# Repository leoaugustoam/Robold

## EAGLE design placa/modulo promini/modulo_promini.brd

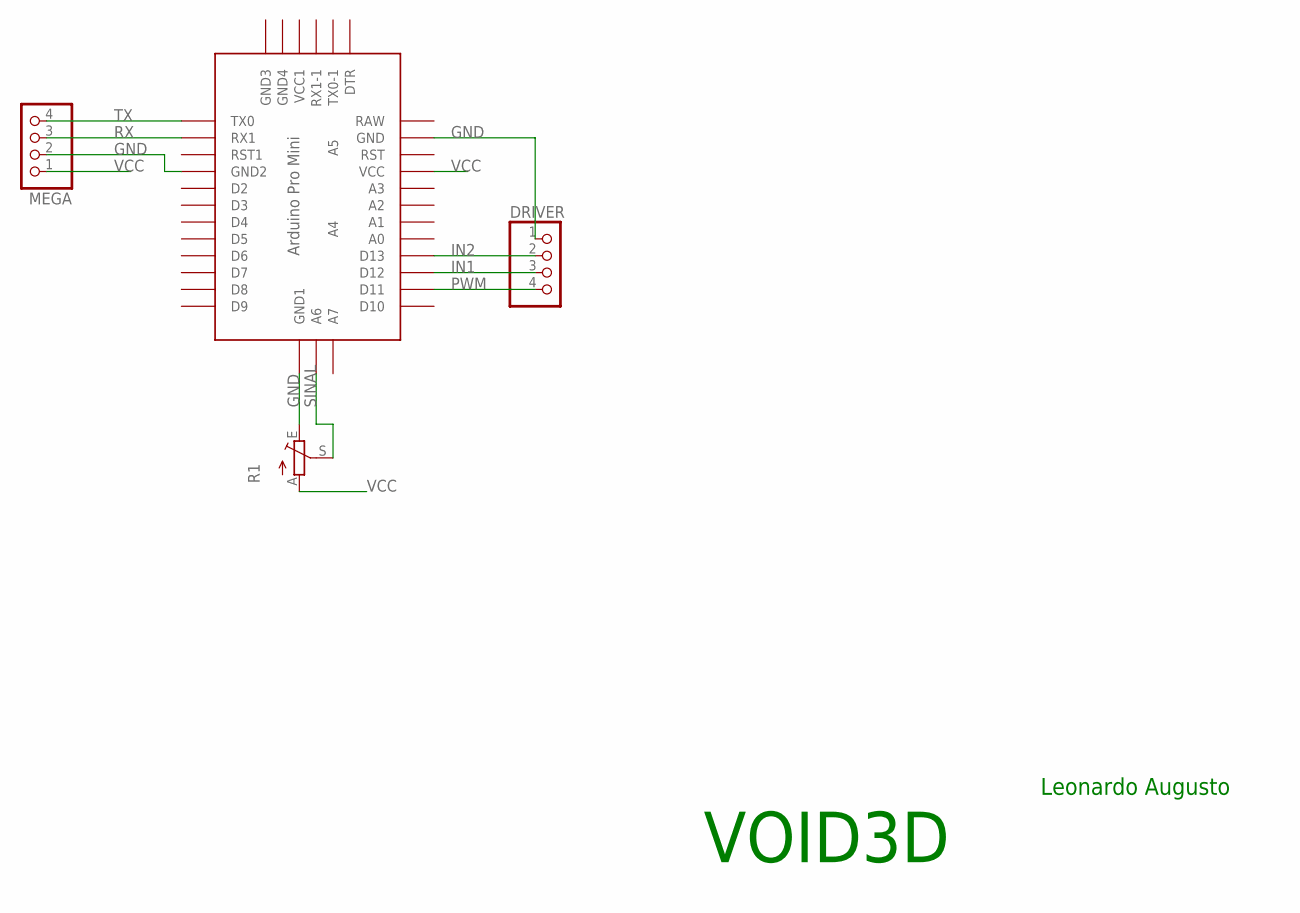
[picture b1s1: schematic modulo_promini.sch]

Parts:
DRIVER: PINHD-1X4; 1X04
MEGA: PINHD-1X4; 1X04
R1: TRIM_EU-CA9V; CA9V
U$1: ABK-PRO-MINI

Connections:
GND: DRIVER.1, MEGA.2, R1.E, U$1.GND, U$1.GND1 (GND2), U$1.GND4 (GND1)
IN1: DRIVER.3, U$1.D12
IN2: DRIVER.2, U$1.D13
PWM: DRIVER.4, U$1.D11
RX: MEGA.3, U$1.RX1
SINAL: R1.S, U$1.A6
TX: MEGA.4, U$1.TX0
VCC: MEGA.1, R1.A, U$1.VCC

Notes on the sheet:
Leonardo Augusto
VOID3D

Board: 2 copper layers, 4 parts (0 on the bottom side), 8 nets, no tracks yet.

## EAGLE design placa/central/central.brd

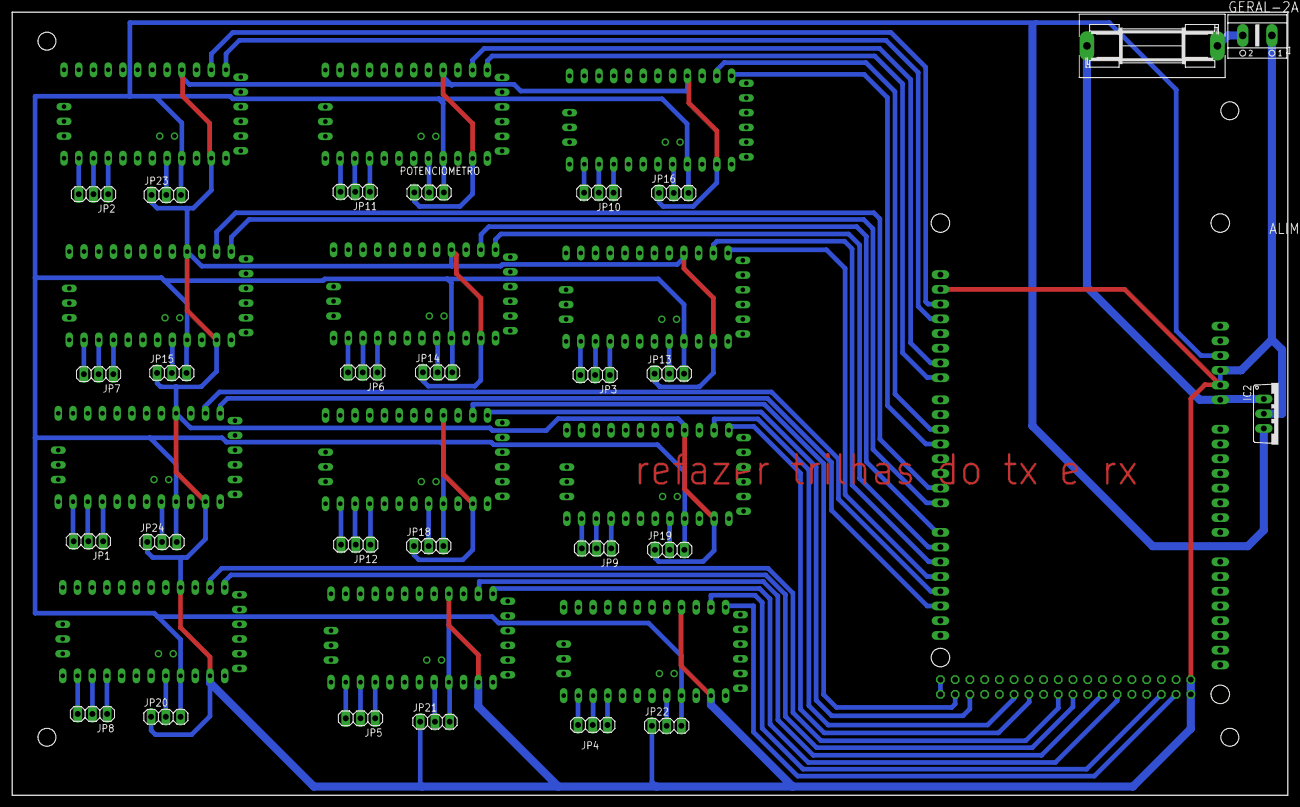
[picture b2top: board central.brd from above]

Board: 2 copper layers, 220.0 x 135.1 mm, 40 parts (1 on the bottom side), 77 nets.

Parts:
ALIMENTACAO: AK500/2
GERAL-2A: SH22,5A
IC1: MEGA_ARDUINO_2
IC2: 7805TV; TO220V
JP1, JP2, JP3, JP4, JP5, JP6, JP7, JP8, JP9, JP10, JP11, JP12, JP13, JP14, JP15, JP16, JP18, JP19, JP20, JP21, JP22, JP23, JP24: 1X03
POTENCIOMETRO: 1X03
U$1, U$2, U$3, U$4, U$5, U$6, U$7, U$8, U$9, U$10, U$11, U$12: ABK-PRO-MINI

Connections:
+5V: IC1.47, IC1.48
GND: ALIMENTACAO.1, IC1.4, IC1.5, IC1.45, IC1.81, IC1.82, IC2.2, JP13.1, JP14.1, JP15.1, JP16.1, JP18.1, JP19.1, JP20.1, JP21.1, JP22.1, JP23.1, JP24.1, POTENCIOMETRO.1, U$1.GND, U$1.GND1, U$2.GND, U$2.GND1, U$3.GND, U$3.GND1, U$4.GND, U$4.GND1, U$5.GND, U$5.GND1, U$6.GND, U$6.GND1, U$7.GND, U$7.GND1, U$8.GND, U$8.GND1, U$9.GND, U$9.GND1, U$10.GND, U$10.GND1, U$11.GND, U$11.GND1, U$12.GND, U$12.GND1
unnamed: JP1.1, U$1.D13
unnamed: JP1.2, U$1.D12
unnamed: JP1.3, U$1.D11
unnamed: JP3.1, U$7.D13
unnamed: JP3.2, U$7.D12
unnamed: JP3.3, U$7.D11
unnamed: JP6.1, U$3.D13
unnamed: JP6.2, U$3.D12
unnamed: JP6.3, U$3.D11
unnamed: JP7.1, U$5.D13
unnamed: JP7.2, U$5.D12
unnamed: JP7.3, U$5.D11
unnamed: JP10.1, U$9.D13
unnamed: JP10.2, U$9.D12
unnamed: JP10.3, U$9.D11
unnamed: JP11.1, U$11.D13
unnamed: JP11.2, U$11.D12
unnamed: JP11.3, U$11.D11
unnamed: JP12.1, U$12.D13
unnamed: JP12.2, U$12.D12
unnamed: JP12.3, U$12.D11
unnamed: JP9.1, U$10.D13
unnamed: JP9.2, U$10.D12
unnamed: JP9.3, U$10.D11
unnamed: JP8.1, U$6.D13
unnamed: JP8.2, U$6.D12
unnamed: JP8.3, U$6.D11
unnamed: JP5.1, U$4.D13
unnamed: JP5.2, U$4.D12
unnamed: JP5.3, U$4.D11
unnamed: JP4.1, U$8.D13
unnamed: JP4.2, U$8.D12
unnamed: JP4.3, U$8.D11
unnamed: JP2.1, U$2.D13
unnamed: JP2.2, U$2.D12
unnamed: JP2.3, U$2.D11
unnamed: JP13.2, U$7.A0
unnamed: JP24.2, U$1.A0
unnamed: JP14.2, U$3.A0
unnamed: JP15.2, U$5.A0
unnamed: JP16.2, U$9.A0
unnamed: POTENCIOMETRO.2, U$11.A0
unnamed: JP18.2, U$12.A0
unnamed: JP19.2, U$10.A0
unnamed: JP20.2, U$6.A0
unnamed: JP21.2, U$4.A0
unnamed: JP22.2, U$8.A0
unnamed: JP23.2, U$2.A0
unnamed: ALIMENTACAO.2, GERAL-2A.1
RX1: IC1.26, U$1.RX1
RX2: IC1.28, U$7.RX1
RX3: IC1.30, U$3.RX1
RX4: IC1.32, U$5.RX1
RX5: IC1.36, U$9.RX1
RX6: IC1.40, U$11.RX1
RX7: IC1.44, U$2.RX1
RX8: IC1.78, U$8.RX1
RX9: IC1.70, U$4.RX1
RX10: IC1.64, U$6.RX1
RX11: IC1.58, U$10.RX1
RX12: IC1.50, U$12.RX1
TX1: IC1.25, U$1.TX0
TX2: IC1.27, U$7.TX0
TX3: IC1.29, U$3.TX0
TX4: IC1.31, U$5.TX0
TX5: IC1.35, U$9.TX0
TX6: IC1.39, U$11.TX0
TX7: IC1.43, U$2.TX0
TX8: IC1.80, U$8.TX0
TX9: IC1.72, U$4.TX0
TX10: IC1.66, U$6.TX0
TX11: IC1.60, U$10.TX0
TX12: IC1.52, U$12.TX0
VCC: IC1.3, IC2.3, JP13.3, JP14.3, JP15.3, JP16.3, JP18.3, JP19.3, JP20.3, JP21.3, JP22.3, JP23.3, JP24.3, POTENCIOMETRO.3, U$1.VCC, U$2.VCC, U$3.VCC, U$4.VCC, U$5.VCC, U$6.VCC, U$7.VCC, U$8.VCC, U$9.VCC, U$10.VCC, U$11.VCC, U$12.VCC
VIN: GERAL-2A.2, IC1.6, IC2.1

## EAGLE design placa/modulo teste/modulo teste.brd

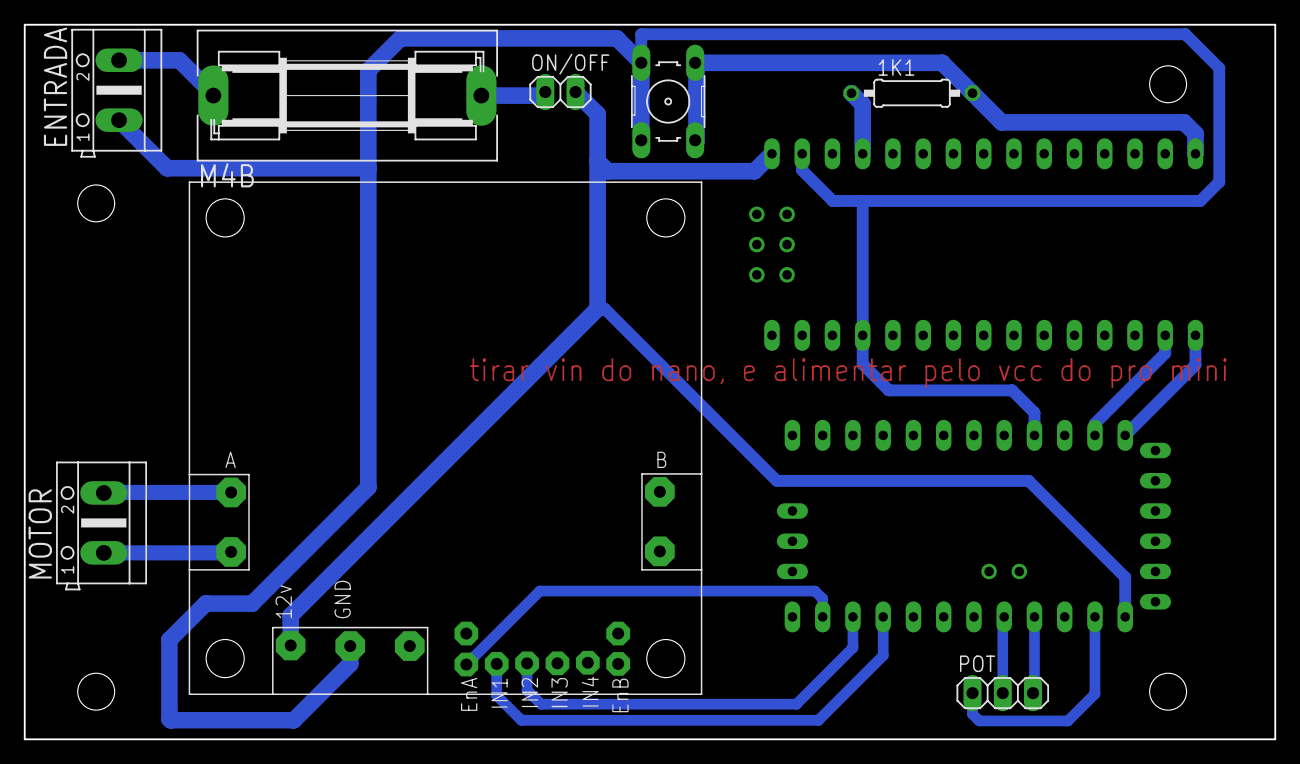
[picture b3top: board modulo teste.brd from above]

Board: 2 copper layers, 105.0 x 60.0 mm, 10 parts (0 on the bottom side), 15 nets.

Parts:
1K1: 0207/10
ENTRADA: AK500/2
M4B: SH22,5A
MOTOR: AK500/2
ON/OFF: 1X02
POT: 1X03
RESET: B3F-10XX
U$1: ABK-PRO-MINI
U$2: L298N
U$3: NANO

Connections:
ENA: U$1.D11, U$2.ENA
GND: ENTRADA.1, POT.1, RESET.3, RESET.4, U$1.GND, U$1.GND1, U$2.GND, U$3.GND, U$3.GND1
IN1: U$1.D13, U$2.IN1
IN2: U$1.D12, U$2.IN2
unnamed: ENTRADA.2, M4B.1
unnamed: M4B.2, ON/OFF.1
unnamed: MOTOR.2, U$2.A1
unnamed: MOTOR.1, U$2.A2
unnamed: POT.2, U$1.A0
unnamed: POT.3, U$1.VCC
unnamed: 1K1.2, RESET.1, RESET.2, U$3.D13
RX: U$1.RX1, U$3.D11
TX: U$1.TX0, U$3.D12
VCC: 1K1.1, U$3.5V
VIN: ON/OFF.2, U$1.RAW, U$2.12V, U$3.RAW

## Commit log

2019-03-12 commit inicial
    codigo responsavel por leitura do controle RF turnigy 9x e controle de 2 motores DC e um servo motor
2019-03-13 adiçao de mais codigos
2019-04-26 atualização
2019-04-26 placa central
2019-05-15 telas iniciais
2020-11-24 ultima versao
